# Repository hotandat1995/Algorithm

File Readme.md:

This folder is where I'm practicing all my concerns about language:
===========
 - C (My mainly language)
 - Python (For write analysis tools)
 - Verilog (Just for fun)

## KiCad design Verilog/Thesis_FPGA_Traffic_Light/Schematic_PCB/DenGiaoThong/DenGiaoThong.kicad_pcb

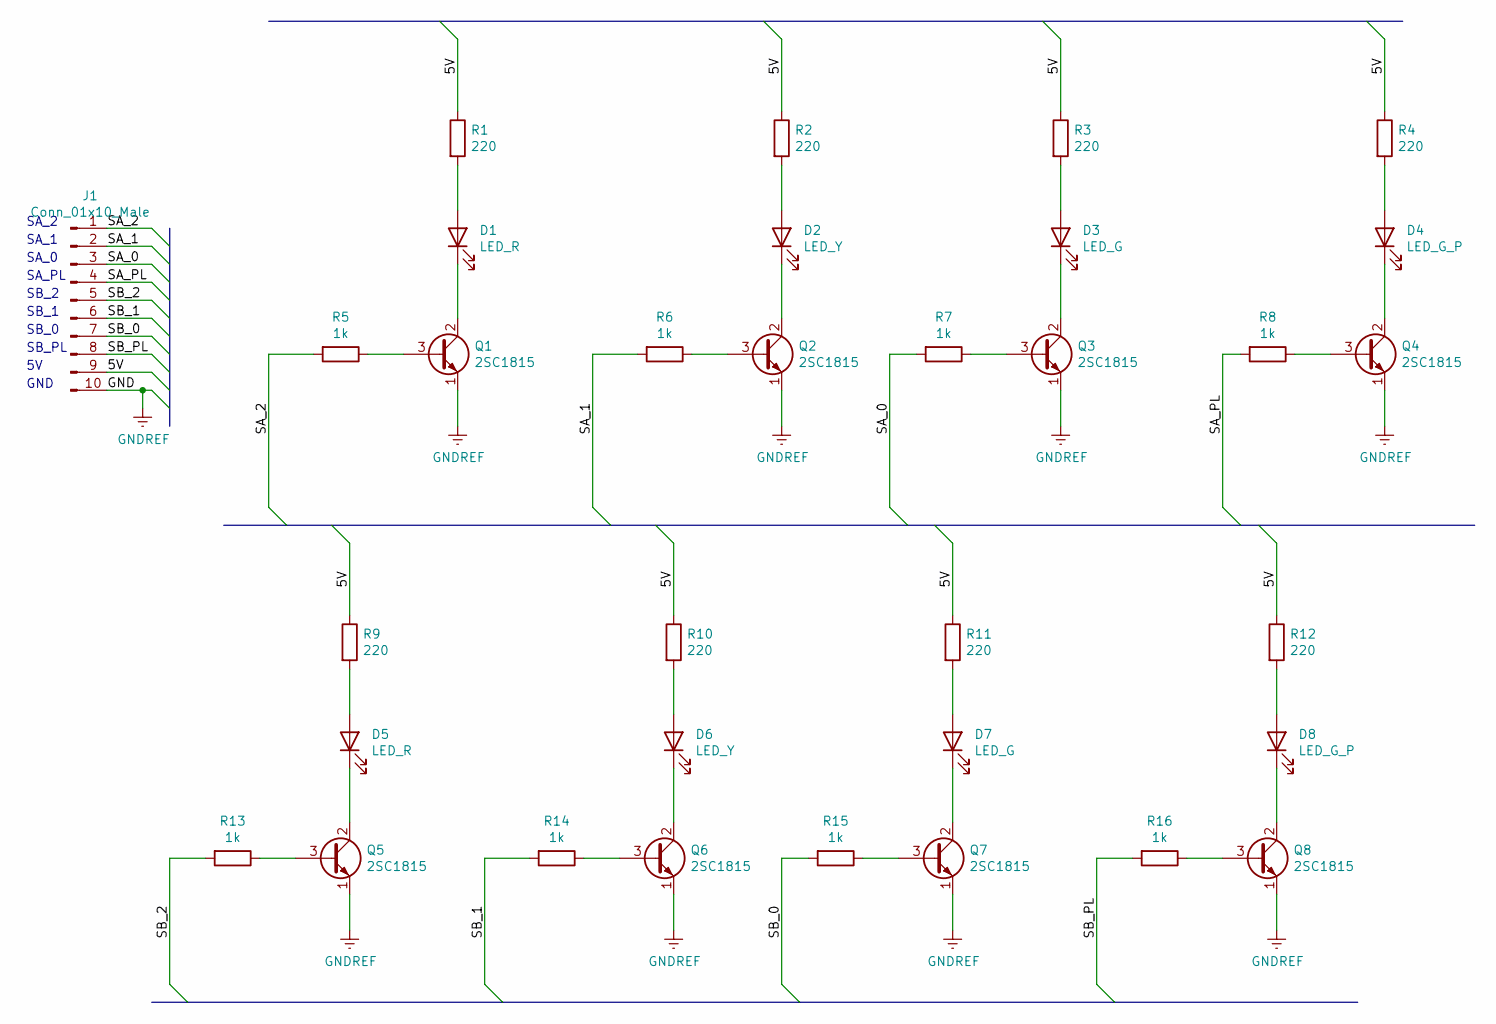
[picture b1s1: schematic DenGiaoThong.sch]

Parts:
D1, D5: LED_R; LED_D3.0mm
D2, D6: LED_Y; LED_D3.0mm
D3, D7: LED_G; LED_D3.0mm
D4, D8: LED_G_P; LED_D3.0mm
J1: Conn_01x10_Male; JST_EH_B10B-EH-A_1x10_P2.50mm_Vertical
Q1, Q2, Q3, Q4, Q5, Q6, Q7, Q8: 2SC1815; TO-92L_Inline_Wide
R1, R2, R3, R4, R9, R10, R11, R12: 220; R_Axial_DIN0411_L9.9mm_D3.6mm_P12.70mm_Horizontal
R5, R6, R7, R8, R13, R14, R15, R16: 1k; R_Axial_DIN0411_L9.9mm_D3.6mm_P12.70mm_Horizontal

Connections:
/5V: J1.9, R1.1, R2.1, R3.1, R4.1, R9.1, R10.1, R11.1, R12.1
/SA_0: J1.3, R7.2
/SA_1: J1.2, R6.2
/SA_2: J1.1, R5.2
/SA_PL: J1.4, R8.2
/SB_0: J1.7, R15.2
/SB_1: J1.6, R14.2
/SB_2: J1.5, R13.2
/SB_PL: J1.8, R16.2
GNDREF: J1.10, Q1.1 (E), Q2.1 (E), Q3.1 (E), Q4.1 (E), Q5.1 (E), Q6.1 (E), Q7.1 (E), Q8.1 (E)
unnamed: D1.1 (K), Q1.2 (C)
unnamed: D1.2 (A), R1.2
unnamed: D2.1 (K), Q2.2 (C)
unnamed: D2.2 (A), R2.2
unnamed: D3.1 (K), Q3.2 (C)
unnamed: D3.2 (A), R3.2
unnamed: D4.1 (K), Q4.2 (C)
unnamed: D4.2 (A), R4.2
unnamed: D5.1 (K), Q5.2 (C)
unnamed: D5.2 (A), R9.2
unnamed: D6.1 (K), Q6.2 (C)
unnamed: D6.2 (A), R10.2
unnamed: D7.1 (K), Q7.2 (C)
unnamed: D7.2 (A), R11.2
unnamed: D8.1 (K), Q8.2 (C)
unnamed: D8.2 (A), R12.2
unnamed: Q1.3 (B), R5.1
unnamed: Q2.3 (B), R6.1
unnamed: Q3.3 (B), R7.1
unnamed: Q4.3 (B), R8.1
unnamed: Q5.3 (B), R13.1
unnamed: Q6.3 (B), R14.1
unnamed: Q7.3 (B), R15.1
unnamed: Q8.3 (B), R16.1

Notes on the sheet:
GND
SA_2
SA_1
SA_0
SA_PL
SB_2
SB_1
SB_0
SB_PL

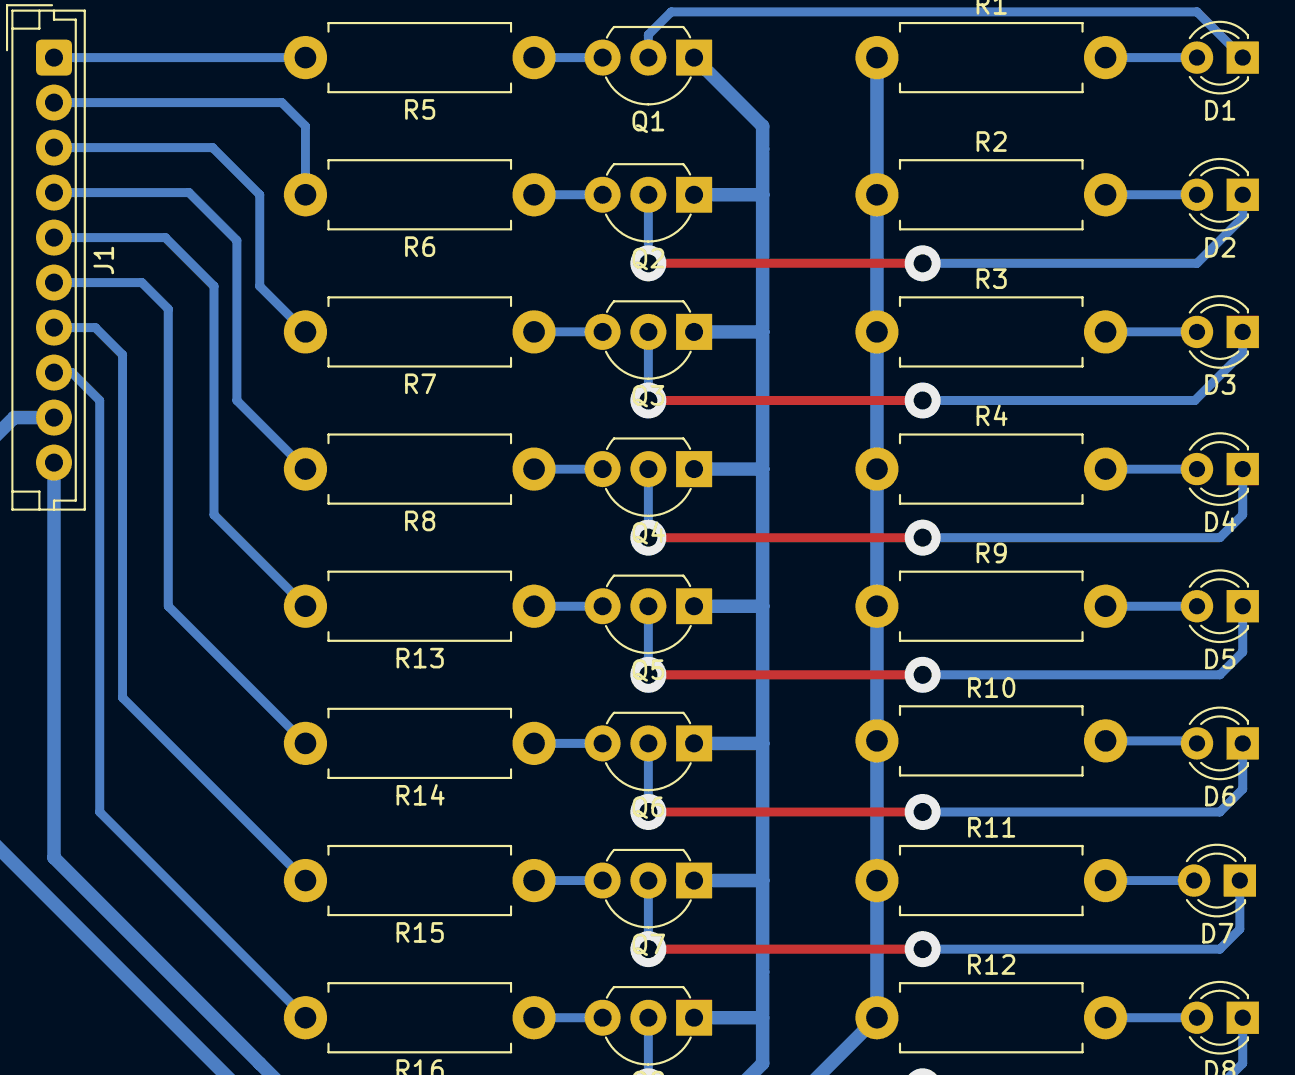
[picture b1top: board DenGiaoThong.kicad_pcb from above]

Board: 2 copper layers, 33 parts (0 on the bottom side), 34 nets.

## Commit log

2019-12-17 update source Linked list
2019-12-17 update source Linked list ver 2
2019-12-18 update Linked list V2
2019-12-19 update llist_rotate_from to Linked_list_ver2
2019-12-19 update double linked list
2019-12-29 update code
2019-12-31 update Doubly linked list
2020-01-02 add free func freeDlist
2020-01-02 update new folder
2020-01-02 modify folder
2020-01-09 update Dlist
2020-06-04 Update source
2020-06-05 update Test Func
2020-06-09 update Scons file
2020-06-10 update Func ptr test
2020-06-10 update Readme and help panel
2020-06-10 add python practice
2020-06-10 update tree
2020-06-19 update json test
2020-06-30 update some new
2020-07-01 update somethings
2020-07-02 update stack and queue
2020-07-27 add new UART_Service for Project and Test package
2020-08-04 update mutex lock and semaphore sample
2020-08-06 update Multi_thread
2020-08-07 update folder structure
2020-08-18 update round buffer
2020-08-19 update circular buffer
2020-08-19 update Mutex, circular buffer, list without next
2020-08-28 update Tes
2020-09-09 update Wifi_master
2020-09-12 update thesis Speech to text
2021-03-18 Update the FPGA folder
2021-03-18 update the output folder for FPGA thesis
2021-03-19 Update fsm.v
    Update the comment for fsm.v
2021-03-19 Update tb_traffic_light.v
    Update comment for testbench file
2021-03-19 Update time_counter.v
    Update comment for time_counter block
2021-03-19 Update Den_Giao_Thong.v
    Update format for Den_Giao_Thong module
2021-03-27 update the truth table with the Priority Lamp
2021-03-27 update folder code for verilog
2021-03-27 update schematic and code for analysis
2021-04-10 update test git ignore
2021-04-10 Add new thesis folder for easy look
2021-04-10 update source code for Verilog thesis traffic light
2021-04-10 update the PCB file and generate PDF
2021-04-10 add workspace file
2021-04-10 add new folder to store Thesis template
2021-04-15 Update bao cao
2021-04-24 Generate the PCB for verilog thesis
2021-05-09 update the Traffic light thesis
